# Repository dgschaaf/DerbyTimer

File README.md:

# DerbyTimer

Pinewood derby timing and race track control system.

**Author:** Darren Schaaf  
**Documentation guide:** [docs/README.md](docs/README.md)

---

## System Overview

DerbyTimer is a two-controller embedded system that manages the complete lifecycle of a pinewood derby race -- from staging and countdown through finish line detection and result display.

```
[Start Controller]  ──── UART 115,200 baud ────  [Finish Controller]
 Arduino Nano (ATmega328P)                         Arduino Nano 33 BLE (nRF52840)
 Custom PCB shield                                 Custom PCB shield
```

The **Start Controller** manages gates, lights, buttons, and race sequencing. The **Finish Controller** measures finish times, drives result displays, and determines the winner. Both run independent state machines that stay synchronized over a serial protocol.

---

## Race Modes

| Mode | Behavior |
|------|----------|
| Gate Drop | Both gates release simultaneously; no reaction time |
| Reaction Time | Cars held at gate; release time measured per lane |
| Pro Tree | Accelerated countdown sequence (400 ms steps) |
| Dial-In | BLE-activated only (Race Manager required); not accessible via the mode button. Pressing Mode while active returns to Gate Drop |

## Race State Flow

```
IDLE -> STAGING -> COUNTDOWN -> RACING -> COMPLETE -> IDLE
```

The Start Controller drives state transitions and notifies the Finish Controller via serial. Mode changes and display advances can also be triggered from the Start Controller.

---

## Start Controller

**Hardware:** Arduino Nano (ATmega328P) on a custom PCB shield  
**Documentation:** [docs/startController.md](docs/startController.md)

### Capabilities

- **Four race modes** with mode-button cycling and per-mode light patterns
- **Dual starting gates** -- electromagnet hold with spring-return solenoid (500 ms activation window)
- **Christmas Tree lights** -- dual 6-light arrays (Blue, Yellowx3, Green, Red) via 74HC595 shift register
- **Reaction time measurement** -- microsecond precision using `micros()` from gate-open to car release
- **Foul detection** -- early release during countdown logged and flagged per lane
- **Four button inputs** -- Start, Mode, Left Lane, Right Lane; hardware-debounced via Schmitt triggers on the PCB shield

Module structure, pin assignments, and timing details:
[docs/startController.md](docs/startController.md).

---

## Finish Controller

**Hardware:** Arduino Nano 33 BLE (nRF52840) on a custom PCB shield  
**Documentation:** [docs/finishController.md](docs/finishController.md)

### Capabilities

- **Optical finish sensors** -- SE61 sensors with 74HC14 Schmitt inverter for clean edges; ISR-driven with configurable active-high/low polarity
- **Minimum race time filter** -- 500 ms suppresses mechanical bounce false triggers
- **Winner determination** -- compares rounded car times; ties supported
- **Dual 5-digit seven-segment displays** -- driven via 74HC238 decoder and MC14543B BCD driver, direct GPIO
- **Display advance** -- Start Controller signals when to cycle from finish time to reaction time view
- **Car time computation** -- reaction time subtracted (normal) or added (foul) from finish time; result rounded to nearest millisecond

Module structure, pin assignments, and display driver details:
[docs/finishController.md](docs/finishController.md).

---

## Serial Communication Protocol

Shared library: `firmware/lib/shared/serialComm.cpp/.h`

12 message types over UART at 115,200 baud with ACK/NACK confirmation and
3-retry / 50 ms timeout. Shared enums (`raceState`, `raceMode`,
`countdownState`) and bitmask constants are defined in
`firmware/lib/shared/raceTypes.h`. Full message table and byte-level wire
format: [docs/protocol.md](docs/protocol.md).

---

## Hardware Design

KiCad schematics and PCB layouts are in `hardware/startBoard/` and `hardware/finishBoard/`.

### Power

| Rail | Purpose |
|------|---------|
| 12V | Electromagnets and Christmas Tree lights |
| 5V | Logic (externally regulated) |
| 3.3V | Reserved (externally regulated) |
| ~1A peak | During gate return solenoid activation |

---

## Testing

Layered strategy -- run the cheapest layer first, escalate to hardware only
when the layer below passes:

- **L1 Static Analysis** -- compile with `--warnings all` + cppcheck
- **L2 Desktop Unit Tests** -- `pio test -e native`; pure logic, no hardware
- **L3 Serial Protocol Tests** -- two cross-wired Nanos (`firmware/fwTest/`)
  or a laptop UART monitor (`firmware/tools/uart_monitor.py`)
- **L4 RACE_TEST Self-Test** -- built-in; hold MODE at power-up
  (codes: [docs/race-test-codes.md](docs/race-test-codes.md))
- **L5 Debug Serial Mode** -- compile with `-DDERBY_DEBUG`
- **Hardware bring-up** -- standalone sketches in `hardware/hwTest/`

Full layer map, directory guide, and run instructions:
[docs/testing.md](docs/testing.md). Two-board bring-up procedure:
[docs/bench-test-protocol.md](docs/bench-test-protocol.md).

---

## Deployment

### Required Libraries

- Standard Arduino libraries (AVR core)
- MBED OS (Nano 33 BLE -- for interrupt support)

### Build

### Option 1 -- VS Code (recommended)

A `.vscode/tasks.json` is included. With the project open in VS Code:

- **Ctrl+Shift+B** -- compiles the Start Controller (default build task)
- **Terminal > Run Task... > Compile Finish Controller** -- compiles the Finish Controller

Requires `arduino-cli` on your PATH.

### Option 2 -- arduino-cli (command line)

```sh
arduino-cli compile --fqbn arduino:avr:nano --library firmware/lib/shared firmware/startController/startController.ino
arduino-cli compile --fqbn arduino:mbed_nano:nano33ble --library firmware/lib/shared firmware/finishController/finishController.ino
```

### Option 3 -- Arduino IDE (not recommended)

The IDE does not know about `firmware/lib/shared`, so opening the `.ino`
directly fails with `serialComm.h: No such file or directory`. To use the
IDE anyway: copy the `firmware/lib/shared/` folder into your sketchbook
`libraries/` folder (e.g. `Documents/Arduino/libraries/shared/`) and re-copy
it after every shared-library change. Boards: Start Controller = Arduino
Nano (ATmega328P); Finish Controller = Arduino Nano 33 BLE. Options 1 and 2
avoid all of this -- prefer them.

### Serial monitoring

Debug builds (`-DDERBY_DEBUG`) log at **115,200** baud. The Finish
Controller's debug output (USB) coexists with live racing -- the wire
protocol runs on Serial1 (D0/D1). The Start Controller's single UART is
shared between USB and the wire protocol: never flash or monitor the SC
over USB with the comm cable connected. Full bench procedure:
[docs/bench-test-protocol.md](docs/bench-test-protocol.md).

---

## Extending the Design

Step-by-step recipes for adding race modes and other maintenance guidelines:
[docs/startController.md](docs/startController.md) (Maintenance Guidelines
section).

---

## Known Limitations

The following are intentional v1.0 scope boundaries, not bugs:

- **BLE / Race Manager** -- The Finish Controller's Nordic radio is unused. BLE integration is planned for the `feature-raceManager` branch. Placeholder call sites are marked `// future:` in source.
- **RFID car identification** -- Not implemented in v1.0. Reserved for the `feature-rfid` branch.
- **Dial-In mode** -- Implemented in firmware but only activatable via BLE from a Race Manager. Cannot be selected via the mode button in standalone operation.
- **Growth feature branches** -- `feature-rfid` and `feature-raceManager` are design and early development branches. They are not merged to main, are not guaranteed to compile, and are not part of v1.0 scope.

---

## Growth Features (In-Progress Branches)

The following capabilities are under active development on separate branches and are not part of the v1.0 release:

### RFID Car Identification (`feature-rfid`)

Dual RC522 RFID readers on the Start Controller shield identify individual cars at staging. Car IDs are transmitted to the Finish Controller and stored in `RaceResults`. This enables per-car timing history and automatic lane assignment.

### Race Manager (`feature-raceManager`)

A Raspberry Pi-based race management system that receives results from the Finish Controller via BLE (Nordic radio on the Nano 33 BLE). The Race Manager software lives in `software/raceManager/` and uses Python and SQLite for race data storage, bracket management, and results reporting.

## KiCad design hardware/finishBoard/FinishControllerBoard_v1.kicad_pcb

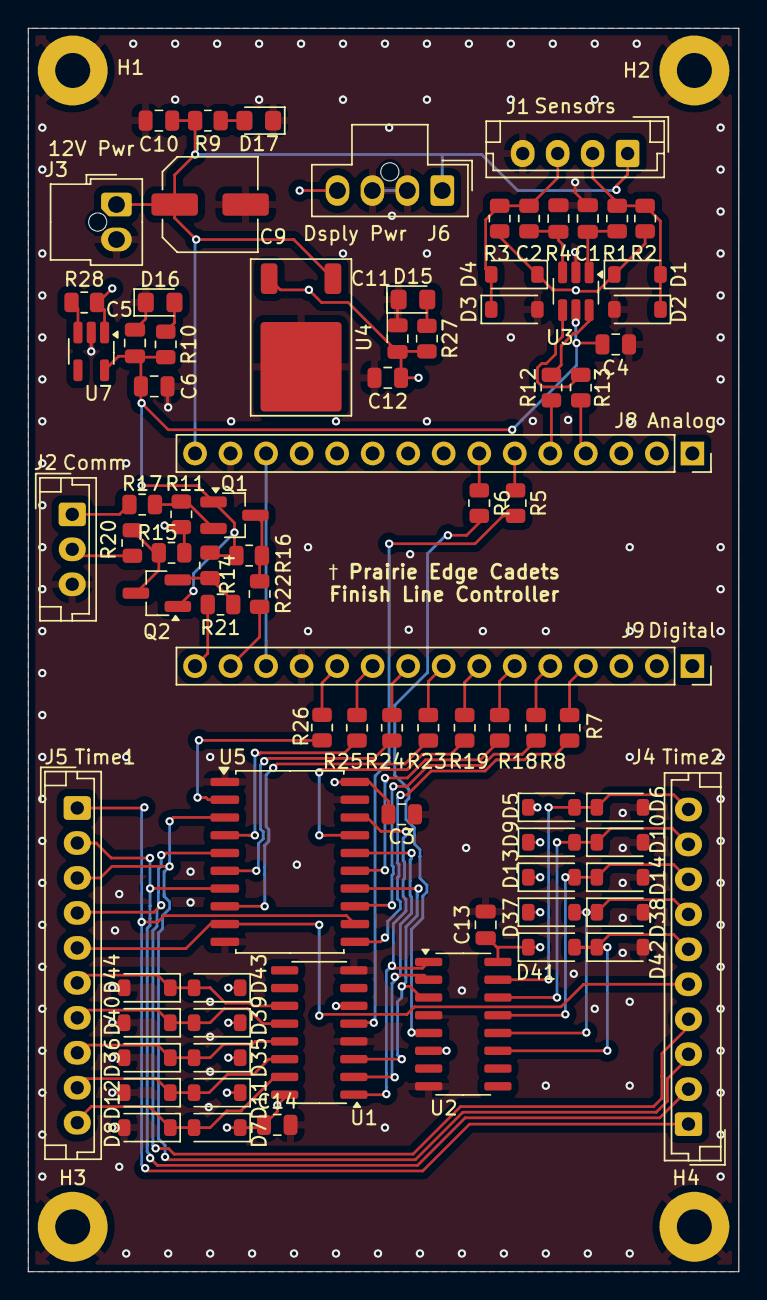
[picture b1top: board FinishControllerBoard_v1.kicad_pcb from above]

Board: 4 copper layers, 50.8 x 88.9 mm, 87 parts (0 on the bottom side), 63 nets.

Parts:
C1, C2, C3, C4, C13, C14: 0.1uF; C_0805_2012Metric
C5, C11: 10uF; C_0805_2012Metric
C6, C10, C12: 10nF; C_0805_2012Metric
C9: 33uF; C_Elec_6.3x7.7
D1, D2, D3, D4, D5, D6, D7, D8, D9, D10, D11, D12, D13, D14, D35, D36, D37, D38, D39, D40, D41, D42, D43, D44: 1N4148W; D_SOD-123
D15, D16, D17: Green; LED_0805_2012Metric_Pad1.15x1.40mm_HandSolder
H1, H2, H3, H4: MountingHole_Pad; MountingHole_2.5mm_Pad
J1: Sensors; JST_EH_B4B-EH-A_1x04_P2.50mm_Vertical
J2: Comm; JST_EH_B3B-EH-A_1x03_P2.50mm_Vertical
J3: 12V Pwr; Molex_Nano-Fit_105309-xx02_1x02_P2.50mm_Vertical
J4: Time2; JST_EH_B10B-EH-A_1x10_P2.50mm_Vertical
J5: Time1; JST_EH_B10B-EH-A_1x10_P2.50mm_Vertical
J6: Dsply Pwr; Molex_Nano-Fit_105309-xx04_1x04_P2.50mm_Vertical
J8: Analog; PinSocket_1x15_P2.54mm_Vertical
J9: Digital; PinSocket_1x15_P2.54mm_Vertical
Q1, Q2: BSS138; SOT-23_Handsoldering
R1, R4, R5, R6, R7, R8, R12, R13, R18, R19, R23, R24, R25, R26: 100; R_0805_2012Metric
R2, R3: 1k; R_0805_2012Metric
R9, R10, R27: 560; R_0805_2012Metric
R11, R14, R15, R16, R28: 10k; R_0805_2012Metric
R17: 150; R_0805_2012Metric
R20, R21, R22: 0; R_0805_2012Metric
U1, U2: 74HCT238; SOIC-16_3.9x9.9mm_P1.27mm
U3: 74LVC2G14; SOT-23-6_Handsoldering
U4: L78M05CDT; TO-252-2
U5: 74HCT244; SOIC-20W_7.5x12.8mm_P1.27mm
U7: AP2112K-3.3; SOT-23-5_HandSoldering

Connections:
+3.3V: C4.2, C5.1, C6.1, Q1.1 (G), Q2.1 (G), R10.2, R14.2, R16.2, U3.5 (VCC), U7.5 (VOUT)
+5V: C3.1, C11.1, C12.1, C13.1, C14.1, D1.1 (K), D3.1 (K), D5.1 (K), D7.1 (K), D9.1 (K), D11.1 (K), D13.1 (K), D35.1 (K), D37.1 (K), D39.1 (K), D41.1 (K), D43.1 (K), J6.4, R2.2, R3.2, R11.2, R15.2, R27.2, R28.2, U1.6 (E3), U1.16 (VCC), U2.6 (E3), U2.16 (VCC), U4.3 (OUT), U5.20 (VCC), U7.1 (VIN)
+12V: C9.1, C10.1, J1.1, J3.1, J6.1, J8.15, R9.2, U4.1 (IN)
/*D3: J9.10, R25.2
/*D5: J9.8, R23.2
/*D6: J9.7, R19.2
/*D9: J9.4, R7.2
/A0: J8.4, R13.1
/A1: J8.5, R12.1
/A2: J8.6, R5.1
/A3: J8.7, R6.1
/D0/RX: J9.14, R22.1
/D1/TX: J9.15, R21.2
/D2: J9.11, R26.2
/D4: J9.9, R24.2
/D7: J9.6, R18.2
/D8: J9.5, R8.2
/FinishSensors/Lane1_FinishLine: R12.2, U3.6
/FinishSensors/Lane2_FinishLine: R13.2, U3.4
/Lane1: D1.2 (A), D2.1 (K), J1.2, R1.1, R2.1
/Lane2: D3.2 (A), D4.1 (K), J1.3, R3.1, R4.1
/Logic Level Shifter/Rx_HV_Out: J2.2, R20.1
/Logic Level Shifter/Tx_HV_In: J2.1, R17.2
/Time1_Hundredths: D11.2 (A), D12.1 (K), J5.9, U1.14 (Y1)
/Time1_Ones: D39.2 (A), D40.1 (K), J5.7, U1.12 (Y3)
/Time1_Tens: D43.2 (A), D44.1 (K), J5.6, U1.11 (Y4)
/Time1_Tenths: D35.2 (A), D36.1 (K), J5.8, U1.13 (Y2)
/Time1_Thousandths: D7.2 (A), D8.1 (K), J5.10, U1.15 (Y0)
/Time2_Hundredths: D9.2 (A), D10.1 (K), J4.9, U2.14 (Y1)
/Time2_Ones: D37.2 (A), D38.1 (K), J4.7, U2.12 (Y3)
/Time2_Tens: D41.2 (A), D42.1 (K), J4.6, U2.11 (Y4)
/Time2_Tenths: D13.2 (A), D14.1 (K), J4.8, U2.13 (Y2)
/Time2_Thousandths: D5.2 (A), D6.1 (K), J4.10, U2.15 (Y0)
/~RESET: J8.13, J9.13
AD0: J4.1, J5.1, U5.12 (1Y3)
AD1: J4.3, J5.3, U5.3 (2Y0)
AD2: J4.4, J5.4, U5.5 (2Y1)
AD3: J4.2, J5.2, U5.7 (2Y2)
BCD_Lane1: R5.2, U1.5 (~E2)
BCD_Lane2: R6.2, U2.5 (~E2)
BCD_MuxA: U1.1 (A0), U2.1 (A0), U5.18 (1Y0)
BCD_MuxB: U1.2 (A1), U2.2 (A1), U5.16 (1Y1)
BCD_MuxC: U1.3 (A2), U2.3 (A2), U5.14 (1Y2)
Decimal_Point: J4.5, J5.5, U5.9 (2Y3)
GND: C1.2, C2.2, C3.2, C4.1, C5.2, C6.2, C9.2, C10.2, C11.2, C12.2, C13.2, C14.2, D2.2 (A), D4.2 (A), D6.2 (A), D8.2 (A), D10.2 (A), D12.2 (A), D14.2 (A), D15.1 (K), D16.1 (K), D17.1 (K), D36.2 (A), D38.2 (A), D40.2 (A), D42.2 (A), D44.2 (A), H1.1, H2.1, H3.1, H4.1, J1.4, J2.3, J3.2, J6.2, J6.3, J8.14, J9.12, U1.4 (~E1), U1.8 (GND), U2.4 (~E1), U2.8 (GND), U3.2 (GND), U4.2, U5.1 (1OE), U5.10 (GND), U5.19 (2OE), U7.2 (GND)
unnamed: C1.1, R1.2, U3.1
unnamed: C2.1, R4.2, U3.3
unnamed: D15.2 (A), R27.1
unnamed: D16.2 (A), R10.1
unnamed: D17.2 (A), R9.1
unnamed: Q1.3 (D), R16.1, R22.2
unnamed: Q1.2 (S), R11.1, R17.1
unnamed: Q2.3 (D), R15.1, R20.2
unnamed: Q2.2 (S), R14.1, R21.1
unnamed: R26.1, U5.2 (1A0)
unnamed: R25.1, U5.4 (1A1)
unnamed: R24.1, U5.6 (1A2)
unnamed: R23.1, U5.8 (1A3)
unnamed: R19.1, U5.17 (2A0)
unnamed: R18.1, U5.15 (2A1)
unnamed: R8.1, U5.13 (2A2)
unnamed: R7.1, U5.11 (2A3)
unnamed: R28.1, U7.3 (EN)

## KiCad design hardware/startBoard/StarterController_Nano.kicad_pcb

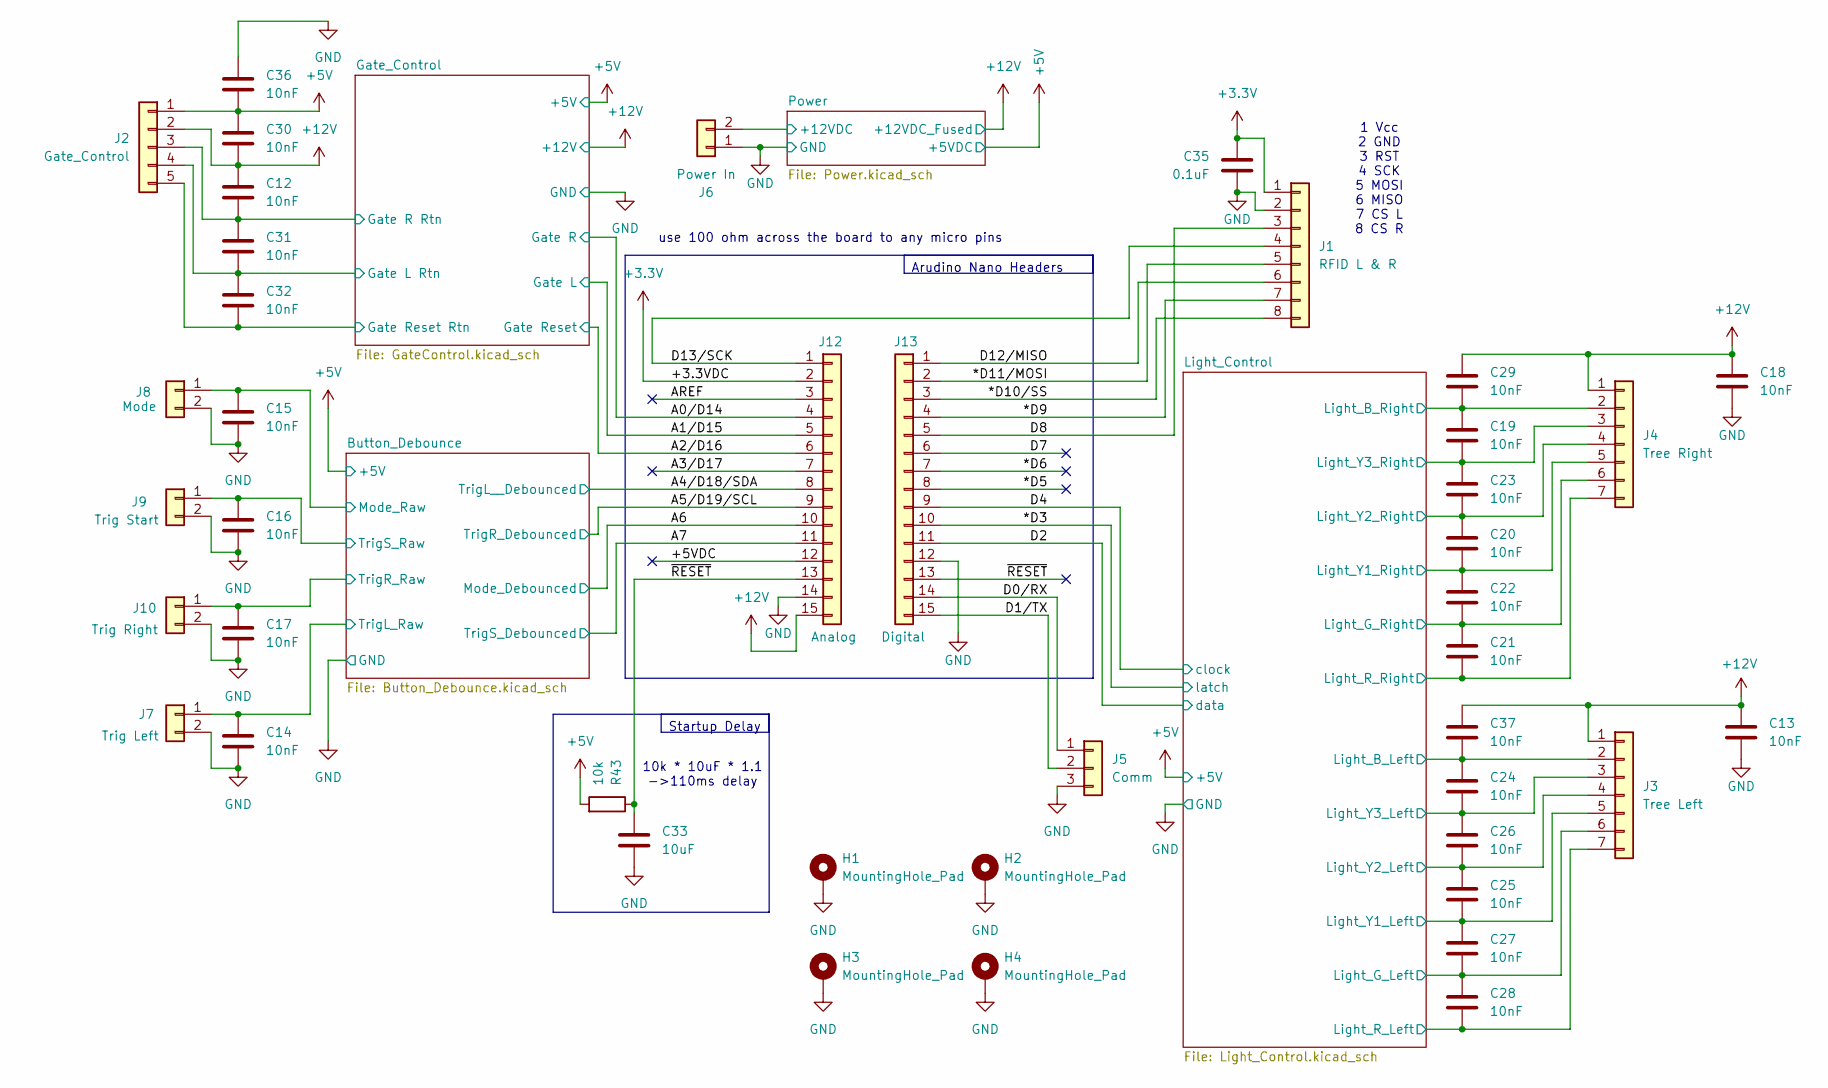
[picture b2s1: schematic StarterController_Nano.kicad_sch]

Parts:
C12, C13, C14, C15, C16, C17, C18, C19, C20, C21, C22, C23, C24, C25, C26, C27, C28, C29, C30, C31, C32, C36, C37: 10nF; C_0805_2012Metric
C33: 10uF; C_0805_2012Metric
C35: 0.1uF; C_0805_2012Metric
H1, H2, H3, H4: MountingHole_Pad; MountingHole_2.5mm_Pad
J1: RFID L & R; JST_EH_B8B-EH-A_1x08_P2.50mm_Vertical
J2: Gate_Control; JST_EH_B5B-EH-A_1x05_P2.50mm_Vertical
J3: Tree Left; JST_EH_B7B-EH-A_1x07_P2.50mm_Vertical
J4: Tree Right; JST_EH_B7B-EH-A_1x07_P2.50mm_Vertical
J5: Comm; JST_EH_B3B-EH-A_1x03_P2.50mm_Vertical
J6: Power In; Molex_Nano-Fit_105309-xx02_1x02_P2.50mm_Vertical
J7: Trig Left; JST_EH_B2B-EH-A_1x02_P2.50mm_Vertical
J8: Mode; JST_EH_B2B-EH-A_1x02_P2.50mm_Vertical
J9: Trig Start; JST_EH_B2B-EH-A_1x02_P2.50mm_Vertical
J10: Trig Right; JST_EH_B2B-EH-A_1x02_P2.50mm_Vertical
J12: Analog; PinSocket_1x15_P2.54mm_Vertical
J13: Digital; PinSocket_1x15_P2.54mm_Vertical
R43: 10k; R_0805_2012Metric

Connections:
+3.3V: C35.1, J1.1, J12.2
+5V: C30.1, C36.2, J2.1, R43.2; also elsewhere on the board
+12V: C12.1, C13.1, C18.1, C29.1, C30.2, C37.1, J2.2, J3.1, J4.1, J12.15; also elsewhere on the board
/*D3: J13.10; also elsewhere on the board
/*D5: J13.8
/*D6: J13.7
/*D9: J1.7, J13.4
/*D10/SS: J1.8, J13.3
/*D11/MOSI: J1.5, J13.2
/+5VDC: J12.12
/A0: J12.4; also elsewhere on the board
/A1: J12.5; also elsewhere on the board
/A2: J12.6; also elsewhere on the board
/A3: J12.7
/A4/SDA: J12.8; also elsewhere on the board
/A5/SCL: J12.9; also elsewhere on the board
/A6: J12.10; also elsewhere on the board
/A7: J12.11; also elsewhere on the board
/AREF: J12.3
/Button_Debounce/Mode_Raw: C15.1, J8.1; also elsewhere on the board
/Button_Debounce/TrigL_Raw: C14.1, J7.1; also elsewhere on the board
/Button_Debounce/TrigR_Raw: C17.1, J10.1; also elsewhere on the board
/Button_Debounce/TrigS_Raw: C16.1, J9.1; also elsewhere on the board
/D0/RX: J5.1, J13.14
/D1/TX: J5.2, J13.15
/D2: J13.11; also elsewhere on the board
/D4: J13.9; also elsewhere on the board
/D7: J13.6
/D8: J1.3, J13.5
/D12/MISO: J1.6, J13.1
/D13/SCK: J1.4, J12.1
/Gate_Control/Gate L Rtn: C31.2, C32.1, J2.4; also elsewhere on the board
/Gate_Control/Gate R Rtn: C12.2, C31.1, J2.3; also elsewhere on the board
/Gate_Control/Gate Reset Rtn: C32.2, J2.5; also elsewhere on the board
/Light_Control/Light_B_Left: C24.1, C37.2, J3.2; also elsewhere on the board
/Light_Control/Light_B_Right: C19.1, C29.2, J4.2; also elsewhere on the board
/Light_Control/Light_G_Left: C27.2, C28.1, J3.6; also elsewhere on the board
/Light_Control/Light_G_Right: C21.1, C22.2, J4.6; also elsewhere on the board
/Light_Control/Light_R_Left: C28.2, J3.7; also elsewhere on the board
/Light_Control/Light_R_Right: C21.2, J4.7; also elsewhere on the board
/Light_Control/Light_Y1_Left: C25.2, C27.1, J3.5; also elsewhere on the board
/Light_Control/Light_Y1_Right: C20.2, C22.1, J4.5; also elsewhere on the board
/Light_Control/Light_Y2_Left: C25.1, C26.2, J3.4; also elsewhere on the board
/Light_Control/Light_Y2_Right: C20.1, C23.2, J4.4; also elsewhere on the board
/Light_Control/Light_Y3_Left: C24.2, C26.1, J3.3; also elsewhere on the board
/Light_Control/Light_Y3_Right: C19.2, C23.1, J4.3; also elsewhere on the board
/Power/+12VDC: J6.2; also elsewhere on the board
/~RESET: C33.1, J12.13, J13.13, R43.1
GND: C13.2, C14.2, C15.2, C16.2, C17.2, C18.2, C33.2, C35.2, C36.1, H1.1, H2.1, H3.1, H4.1, J1.2, J5.3, J6.1, J7.2, J8.2, J9.2, J10.2, J12.14, J13.12; also elsewhere on the board

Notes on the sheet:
1 Vcc 2 GND 3 RST 4 SCK 5 MOSI 6 MISO 7 CS L 8 CS R
10k * 10uF * 1.1 ->110ms delay
use 100 ohm across the board to any micro pins
Arudino Nano Headers
Startup Delay

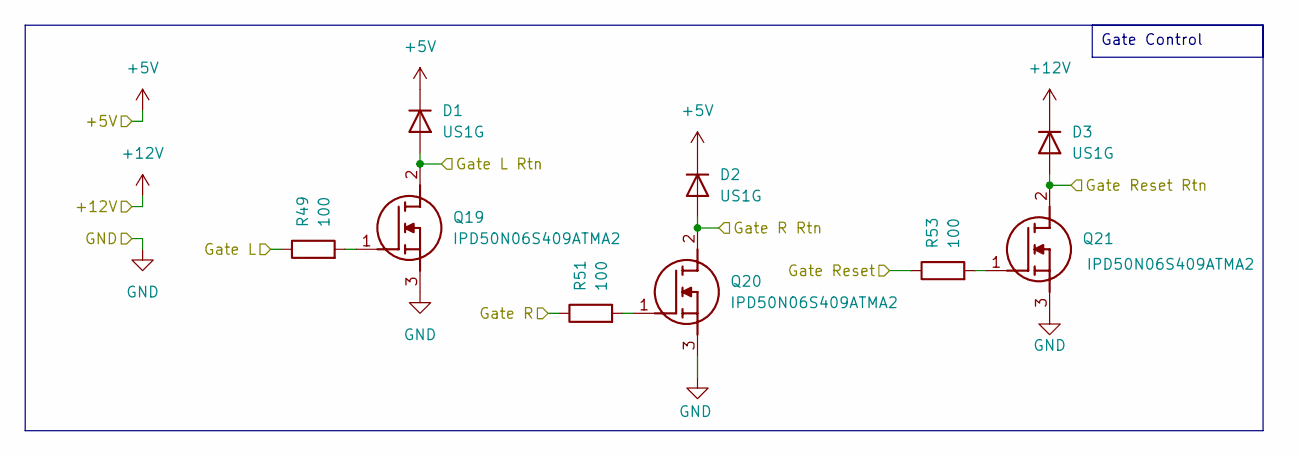
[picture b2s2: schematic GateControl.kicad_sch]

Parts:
D1, D2, D3: US1G; D_SMA
Q19, Q20, Q21: IPD50N06S409ATMA2; TO-252-3_TabPin2; Mouser Part Number 726-IPD50N06S409ATMA
R49, R51, R53: 100; R_0805_2012Metric

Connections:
+5V: D1.1 (K), D2.1 (K); also elsewhere on the board
+12V: D3.1 (K); also elsewhere on the board
/A0: R51.1; also elsewhere on the board
/A1: R49.1; also elsewhere on the board
/A2: R53.1; also elsewhere on the board
/Gate_Control/Gate L Rtn: D1.2 (A), Q19.2 (D); also elsewhere on the board
/Gate_Control/Gate R Rtn: D2.2 (A), Q20.2 (D); also elsewhere on the board
/Gate_Control/Gate Reset Rtn: D3.2 (A), Q21.2 (D); also elsewhere on the board
GND: Q19.3 (S), Q20.3 (S), Q21.3 (S); also elsewhere on the board
unnamed: Q19.1 (G), R49.2
unnamed: Q20.1 (G), R51.2
unnamed: Q21.1 (G), R53.2

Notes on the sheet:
Gate Control

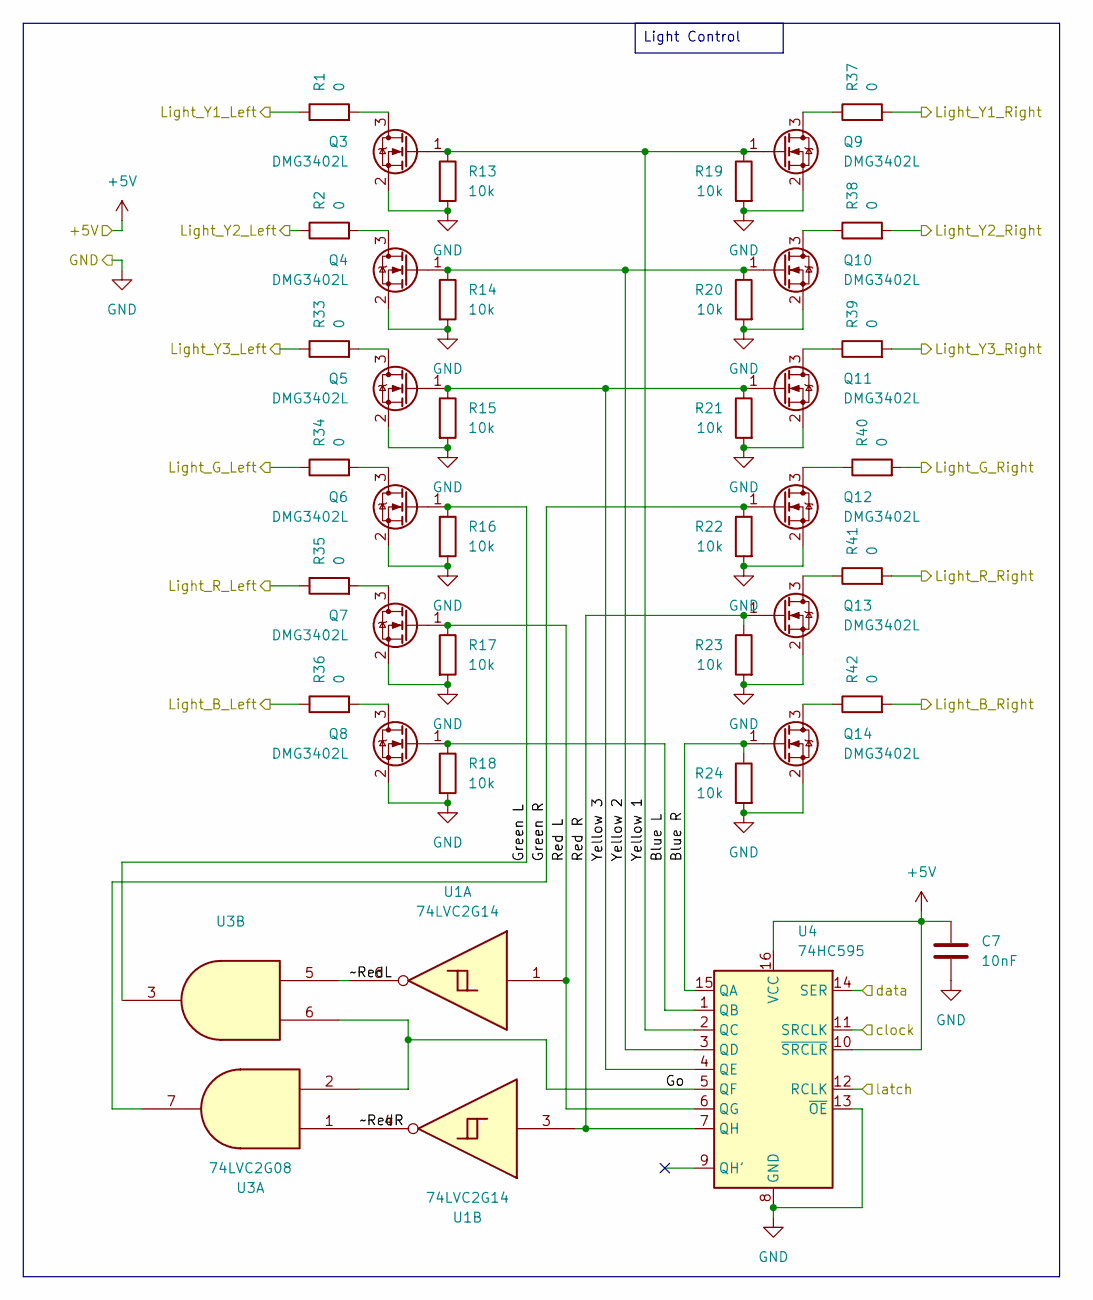
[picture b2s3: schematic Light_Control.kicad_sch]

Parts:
C7: 10nF; C_0805_2012Metric
Q3, Q4, Q5, Q6, Q7, Q8, Q9, Q10, Q11, Q12, Q13, Q14: DMG3402L; SOT-23-3
R1, R2, R33, R34, R35, R36, R37, R38, R39, R40, R41, R42: 0; R_0805_2012Metric
R13, R14, R15, R16, R17, R18, R19, R20, R21, R22, R23, R24: 10k; R_0805_2012Metric
U1: 74LVC2G14; SOT-363_SC-70-6
U3: 74LVC2G08; SSOP-8_2.95x2.8mm_P0.65mm
U4: 74HC595; SOIC-16_3.9x9.9mm_P1.27mm

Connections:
+5V: C7.1, U4.10 (~SRCLR), U4.16 (VCC); also elsewhere on the board
/*D3: U4.12 (RCLK); also elsewhere on the board
/D2: U4.14 (SER); also elsewhere on the board
/D4: U4.11 (SRCLK); also elsewhere on the board
/Light_Control/Blue L: Q8.1 (G), R18.1, U4.1 (QB)
/Light_Control/Blue R: Q14.1 (G), R24.1, U4.15 (QA)
/Light_Control/Go: U3.2, U3.6, U4.5 (QF)
/Light_Control/Green L: Q6.1 (G), R16.1, U3.3
/Light_Control/Green R: Q12.1 (G), R22.1, U3.7
/Light_Control/Light_B_Left: R36.1; also elsewhere on the board
/Light_Control/Light_B_Right: R42.2; also elsewhere on the board
/Light_Control/Light_G_Left: R34.1; also elsewhere on the board
/Light_Control/Light_G_Right: R40.2; also elsewhere on the board
/Light_Control/Light_R_Left: R35.1; also elsewhere on the board
/Light_Control/Light_R_Right: R41.2; also elsewhere on the board
/Light_Control/Light_Y1_Left: R1.1; also elsewhere on the board
/Light_Control/Light_Y1_Right: R37.2; also elsewhere on the board
/Light_Control/Light_Y2_Left: R2.1; also elsewhere on the board
/Light_Control/Light_Y2_Right: R38.2; also elsewhere on the board
/Light_Control/Light_Y3_Left: R33.1; also elsewhere on the board
/Light_Control/Light_Y3_Right: R39.2; also elsewhere on the board
/Light_Control/Red L: Q7.1 (G), R17.1, U1.1, U4.6 (QG)
/Light_Control/Red R: Q13.1 (G), R23.1, U1.3, U4.7 (QH)
/Light_Control/Yellow 1: Q3.1 (G), Q9.1 (G), R13.1, R19.1, U4.2 (QC)
/Light_Control/Yellow 2: Q4.1 (G), Q10.1 (G), R14.1, R20.1, U4.3 (QD)
/Light_Control/Yellow 3: Q5.1 (G), Q11.1 (G), R15.1, R21.1, U4.4 (QE)
/Light_Control/~RedL: U1.6, U3.5
/Light_Control/~RedR: U1.4, U3.1
GND: C7.2, Q3.2 (S), Q4.2 (S), Q5.2 (S), Q6.2 (S), Q7.2 (S), Q8.2 (S), Q9.2 (S), Q10.2 (S), Q11.2 (S), Q12.2 (S), Q13.2 (S), Q14.2 (S), R13.2, R14.2, R15.2, R16.2, R17.2, R18.2, R19.2, R20.2, R21.2, R22.2, R23.2, R24.2, U4.8 (GND), U4.13 (~OE); also elsewhere on the board
unnamed: Q3.3 (D), R1.2
unnamed: Q4.3 (D), R2.2
unnamed: Q5.3 (D), R33.2
unnamed: Q6.3 (D), R34.2
unnamed: Q7.3 (D), R35.2
unnamed: Q8.3 (D), R36.2
unnamed: Q9.3 (D), R37.1
unnamed: Q10.3 (D), R38.1
unnamed: Q11.3 (D), R39.1
unnamed: Q12.3 (D), R40.1
unnamed: Q13.3 (D), R41.1
unnamed: Q14.3 (D), R42.1

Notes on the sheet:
Light Control

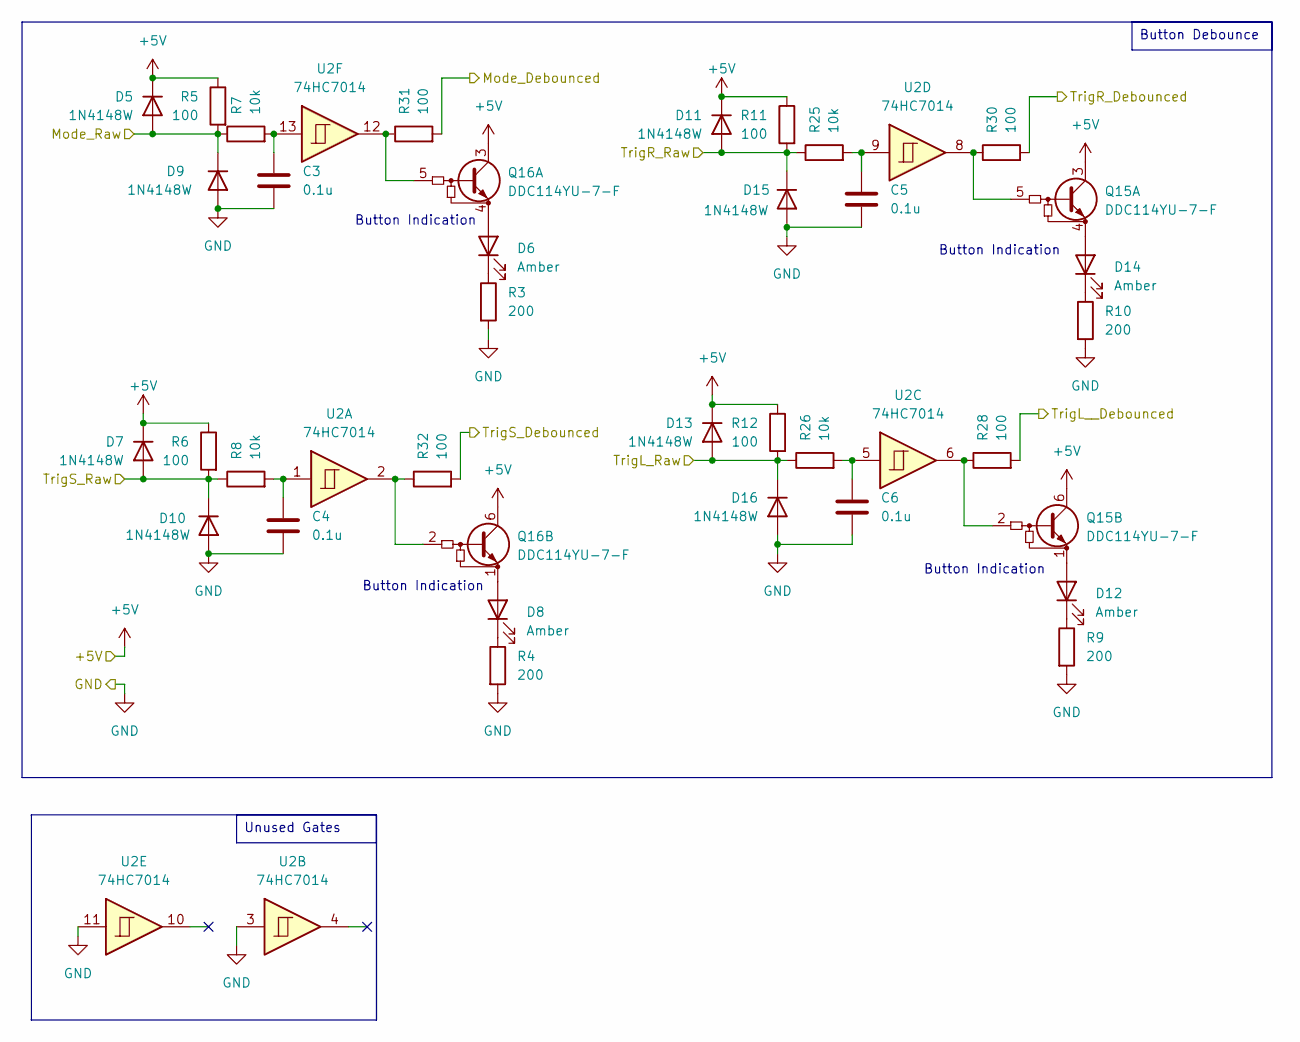
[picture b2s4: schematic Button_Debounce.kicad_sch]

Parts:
C3, C4, C5, C6: 0.1u; C_0805_2012Metric
D5, D7, D9, D10, D11, D13, D15, D16: 1N4148W; D_SOD-123
D6, D8, D12, D14: Amber; LED_0805_2012Metric
Q15, Q16: DDC114YU-7-F; SOT-363_SC-70-6
R3, R4, R9, R10: 200; R_0805_2012Metric
R5, R6, R11, R12, R28, R30, R31, R32: 100; R_0805_2012Metric
R7, R8, R25, R26: 10k; R_0805_2012Metric
U2: 74HC7014; SOIC-14_3.9x8.7mm_P1.27mm

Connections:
+5V: D5.1 (K), D7.1 (K), D11.1 (K), D13.1 (K), Q15.3 (C1), Q15.6 (C1), Q16.3 (C1), Q16.6 (C1), R5.1, R6.1, R11.1, R12.1; also elsewhere on the board
/A4/SDA: R28.2; also elsewhere on the board
/A5/SCL: R30.2; also elsewhere on the board
/A6: R31.2; also elsewhere on the board
/A7: R32.2; also elsewhere on the board
/Button_Debounce/Mode_Raw: D5.2 (A), D9.1 (K), R5.2, R7.1; also elsewhere on the board
/Button_Debounce/TrigL_Raw: D13.2 (A), D16.1 (K), R12.2, R26.1; also elsewhere on the board
/Button_Debounce/TrigR_Raw: D11.2 (A), D15.1 (K), R11.2, R25.1; also elsewhere on the board
/Button_Debounce/TrigS_Raw: D7.2 (A), D10.1 (K), R6.2, R8.1; also elsewhere on the board
GND: C3.2, C4.2, C5.2, C6.2, D9.2 (A), D10.2 (A), D15.2 (A), D16.2 (A), R3.2, R4.2, R9.2, R10.2, U2.3, U2.11; also elsewhere on the board
unnamed: C3.1, R7.2, U2.13
unnamed: C4.1, R8.2, U2.1
unnamed: C5.1, R25.2, U2.9
unnamed: C6.1, R26.2, U2.5
unnamed: D6.2 (A), Q16.4 (E1)
unnamed: D6.1 (K), R3.1
unnamed: D8.2 (A), Q16.1 (E1)
unnamed: D8.1 (K), R4.1
unnamed: D12.2 (A), Q15.1 (E1)
unnamed: D12.1 (K), R9.1
unnamed: D14.2 (A), Q15.4 (E1)
unnamed: D14.1 (K), R10.1
unnamed: Q15.5 (B1), R30.1, U2.8
unnamed: Q15.2 (B1), R28.1, U2.6
unnamed: Q16.5 (B1), R31.1, U2.12
unnamed: Q16.2 (B1), R32.1, U2.2

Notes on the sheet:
Button Indication
Unused Gates
Button Debounce

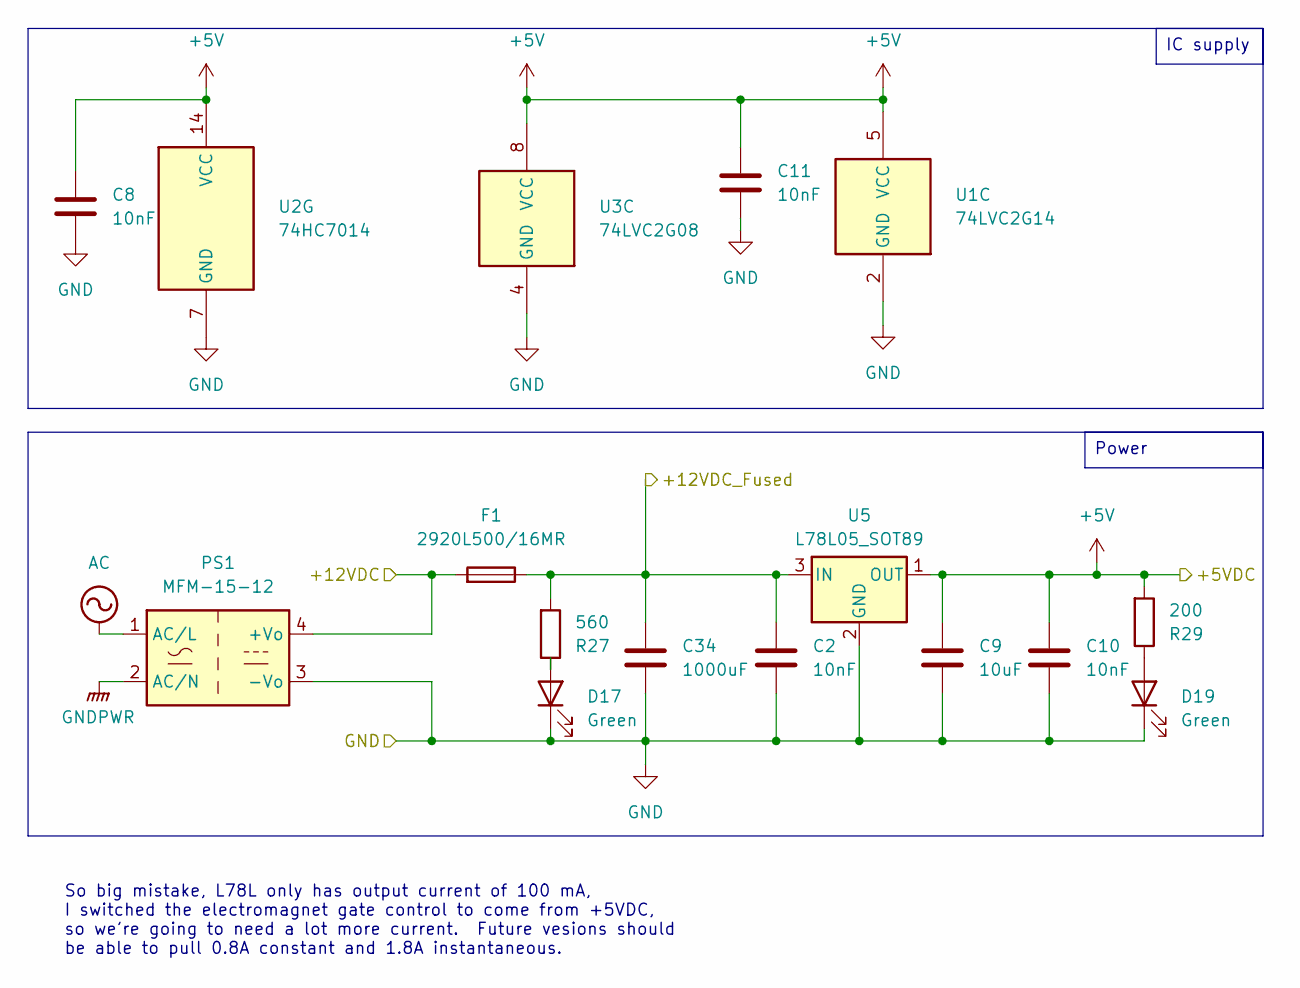
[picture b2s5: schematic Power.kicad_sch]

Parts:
C2, C8, C10, C11: 10nF; C_0805_2012Metric
C9: 10uF; C_0805_2012Metric
C34: 1000uF; C_Elec_10x10.2
D17, D19: Green; LED_0805_2012Metric
F1: 2920L500/16MR; Fuse_2920_7451Metric
PS1: MFM-15-12; Converter_ACDC_MeanWell_MFM-15-xx_THT
R27: 560; R_0805_2012Metric
R29: 200; R_0805_2012Metric
U1: 74LVC2G14; SOT-363_SC-70-6
U2: 74HC7014; SOIC-14_3.9x8.7mm_P1.27mm
U3: 74LVC2G08; SSOP-8_2.95x2.8mm_P0.65mm
U5: L78L05_SOT89; SOT-89-3

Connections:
+5V: C8.1, C9.1, C10.1, C11.1, R29.2, U1.5 (VCC), U2.14 (VCC), U3.8 (VCC), U5.1 (OUT); also elsewhere on the board
+12V: C2.1, C34.1, F1.1, R27.2, U5.3 (IN); also elsewhere on the board
/Power/+12VDC: F1.2, PS1.4 (+Vo); also elsewhere on the board
GND: C2.2, C8.2, C9.2, C10.2, C11.2, C34.2, D17.1 (K), D19.1 (K), PS1.3 (-Vo), U1.2 (GND), U2.7 (GND), U3.4 (GND), U5.2 (GND); also elsewhere on the board
unnamed: D17.2 (A), R27.1
unnamed: D19.2 (A), R29.1

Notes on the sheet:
So big mistake, L78L only has output current of 100 mA, I switched the electromagnet gate control to come from +5VDC, so we're going to need a lot more current. Future vesions should be able to pull 0.8A constant and 1.8A instantaneous.
IC supply
Power

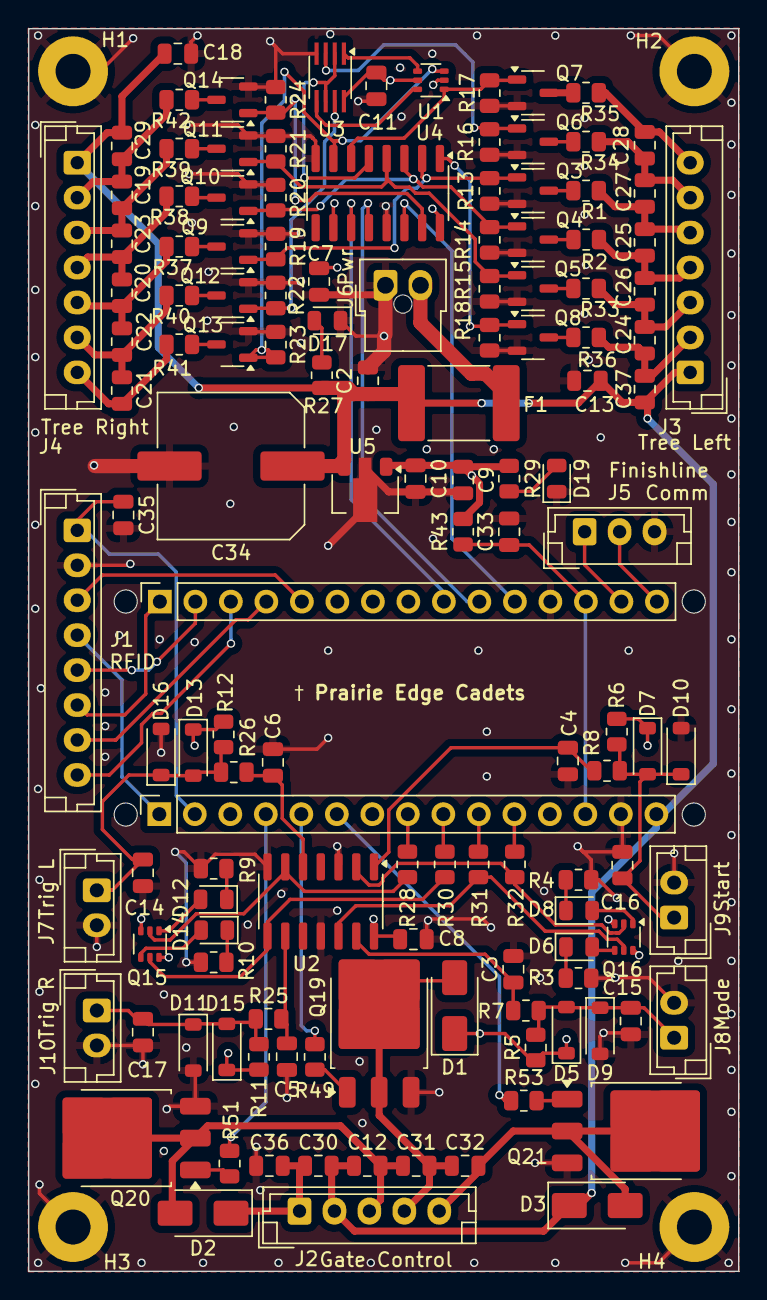
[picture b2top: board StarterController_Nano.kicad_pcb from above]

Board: 4 copper layers, 50.8 x 88.9 mm, 142 parts (0 on the bottom side), 88 nets.

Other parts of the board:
MH1, MH2, MH3, MH4: MountingHole_65mil

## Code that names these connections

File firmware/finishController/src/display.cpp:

#include <Arduino.h>
#include "display.h"

// -------------------------------------------
//  PIN DEFINITIONS  (match your schematic)
// -------------------------------------------
static constexpr uint8_t PIN_BCD_MUX_A = 2;   // D2
static constexpr uint8_t PIN_BCD_MUX_B = 3;   // D3
static constexpr uint8_t PIN_BCD_MUX_C = 4;   // D4

static constexpr uint8_t PIN_AD0 = 5;         // D5
static constexpr uint8_t PIN_AD1 = 6;         // D6
static constexpr uint8_t PIN_AD2 = 7;         // D7
static constexpr uint8_t PIN_AD3 = 8;         // D8

static constexpr uint8_t PIN_DECIMAL = 9;     // D9

// Lane select -> goes to 74HC238 EN inputs
static constexpr uint8_t PIN_LANE1 = A2;      // BCD_Lane1 (E2 on U1)
static constexpr uint8_t PIN_LANE2 = A3;      // BCD_Lane2 (E2 on U2)

// Digit index mapping (0-4 -> tens, ones, tenths, hundredths, thousandths)
static constexpr uint8_t NUM_DIGITS = DISPLAY_NUM_DIGITS;

// -------------------------------------------
void setupDisplay() {
    pinMode(PIN_BCD_MUX_A, OUTPUT);
    pinMode(PIN_BCD_MUX_B, OUTPUT);
    pinMode(PIN_BCD_MUX_C, OUTPUT);

    pinMode(PIN_AD0, OUTPUT);
    pinMode(PIN_AD1, OUTPUT);
    pinMode(PIN_AD2, OUTPUT);
    pinMode(PIN_AD3, OUTPUT);

    pinMode(PIN_DECIMAL, OUTPUT);

    pinMode(PIN_LANE1, OUTPUT);
    pinMode(PIN_LANE2, OUTPUT);

    // Default: clear everything
    digitalWrite(PIN_DECIMAL, LOW);
    digitalWrite(PIN_LANE1, HIGH);
    digitalWrite(PIN_LANE2, HIGH);

    // Clear both displays on boot
    updateDisplay(0, LANE_LEFT);
    updateDisplay(0, LANE_RIGHT);
}

// -------------------------------------------
static void writeDigit(uint8_t idx, uint8_t val, bool showDecimal) {

    // Decimal point
    digitalWrite(PIN_DECIMAL, showDecimal ? HIGH : LOW);

    // Digit index -> A0/A1/A2
    digitalWrite(PIN_BCD_MUX_A, (idx & 0x01));
    digitalWrite(PIN_BCD_MUX_B, (idx & 0x02));
    digitalWrite(PIN_BCD_MUX_C, (idx & 0x04));

    // BCD lines
    digitalWrite(PIN_AD0, (val & 0x01));
    digitalWrite(PIN_AD1, (val & 0x02));
    digitalWrite(PIN_AD2, (val & 0x04));
    digitalWrite(PIN_AD3, (val & 0x08));

    // The 238 output latches the digit automatically.
    delayMicroseconds(30);  // plenty for MC14543 latch
}

// -------------------------------------------
void updateDisplay(uint32_t timeUs, Lane lane) {

    uint8_t d[NUM_DIGITS];
    extractDisplayDigits(timeUs, d);    // round to ms, clamp, split into BCD digits

    // Lane enable (E2 = HIGH to activate)
    if (lane == LANE_LEFT) {
        digitalWrite(PIN_LANE1, LOW);
        digitalWrite(PIN_LANE2, HIGH);
    } else {
        digitalWrite(PIN_LANE1, HIGH);
        digitalWrite(PIN_LANE2, LOW);
    }

    for (uint8_t i = 0; i < NUM_DIGITS; ++i) {
        bool dec = (i == 1);
        writeDigit(i, d[i], dec);
    }

    // Disable both lanes afterward
    digitalWrite(PIN_LANE1, HIGH);
    digitalWrite(PIN_LANE2, HIGH);
}

static void writeBlankDigit(uint8_t idx)
{
    // Disable decimal
    digitalWrite(PIN_DECIMAL, LOW);

    // Select digit index
    digitalWrite(PIN_BCD_MUX_A, (idx & 0x01));
    digitalWrite(PIN_BCD_MUX_B, (idx & 0x02));
    digitalWrite(PIN_BCD_MUX_C, (idx & 0x04));

    // BCD = 1111 -> blank segment output on MC14543
    digitalWrite(PIN_AD0, HIGH);
    digitalWrite(PIN_AD1, HIGH);
    digitalWrite(PIN_AD2, HIGH);
    digitalWrite(PIN_AD3, HIGH);

    delayMicroseconds(30);
}

void clearDisplay(Lane lane)
{
    // ACTIVE LOW enable logic
    if (lane == LANE_LEFT) {
        digitalWrite(PIN_LANE1, LOW);
        digitalWrite(PIN_LANE2, HIGH);
    } else {
        digitalWrite(PIN_LANE1, HIGH);
        digitalWrite(PIN_LANE2, LOW);
    }

    for (uint8_t i = 0; i < NUM_DIGITS; i++) {
        writeBlankDigit(i);
    }

    // Disable both
    digitalWrite(PIN_LANE1, HIGH);
    digitalWrite(PIN_LANE2, HIGH);
}
